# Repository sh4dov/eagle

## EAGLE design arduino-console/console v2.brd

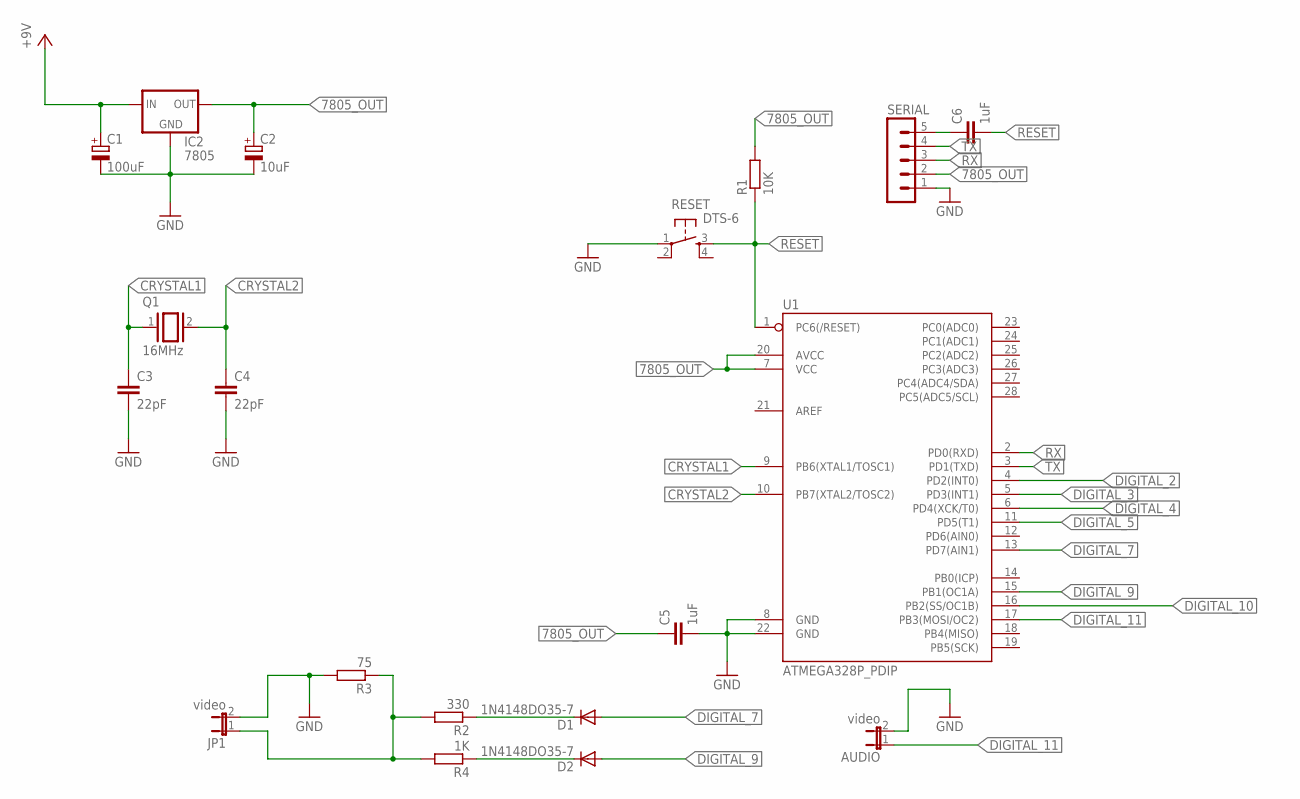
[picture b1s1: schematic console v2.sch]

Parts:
AUDIO: video; JP1
C1: 100uF; E2,5-6E
C2: 10uF; E2,5-6E
C3, C4: 22pF; C2.5-3
C5, C6: 1uF; C2.5-3
D1, D2: 1N4148DO35-7; DO35-7
IC2: 7805; 78MXXL
JP1: video; JP1
Q1: 16MHz; QS
R1: 10K; 0204/5
R2: 330; 0204/5
R3: 75; 0204/5
R4: 1K; 0204/5
RESET: DTS-6
SERIAL: MA05-1
U1: ATMEGA328P_PDIP; DIL28-3

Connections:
7805_OUT: C2.+, C5.1, IC2.OUT, R1.2, SERIAL.2, U1.7 (VCC), U1.20 (AVCC)
CRYSTAL1: C3.1, Q1.1, U1.9 (PB6(XTAL1/TOSC1))
CRYSTAL2: C4.1, Q1.2, U1.10 (PB7(XTAL2/TOSC2))
DIGITAL_2: U1.4 (PD2(INT0))
DIGITAL_3: U1.5 (PD3(INT1))
DIGITAL_4: U1.6 (PD4(XCK/T0))
DIGITAL_5: U1.11 (PD5(T1))
DIGITAL_7: D1.A, U1.13 (PD7(AIN1))
DIGITAL_9: D2.A, U1.15 (PB1(OC1A))
DIGITAL_10: U1.16 (PB2(SS/OC1B))
DIGITAL_11: AUDIO.1, U1.17 (PB3(MOSI/OC2))
GND: AUDIO.2, C1.-, C2.-, C3.2, C4.2, C5.2, IC2.GND, JP1.2, R3.2, RESET.1, SERIAL.1, U1.8 (GND), U1.22 (GND)
unnamed: D1.C, R2.1
unnamed: D2.C, R4.1
unnamed: JP1.1, R2.2, R3.1, R4.2
unnamed: C6.1, SERIAL.5
RESET: C6.2, R1.1, RESET.3, U1.1 (PC6(/RESET))
RX: SERIAL.3, U1.2 (PD0(RXD))
TX: SERIAL.4, U1.3 (PD1(TXD))
VCC: C1.+, IC2.IN

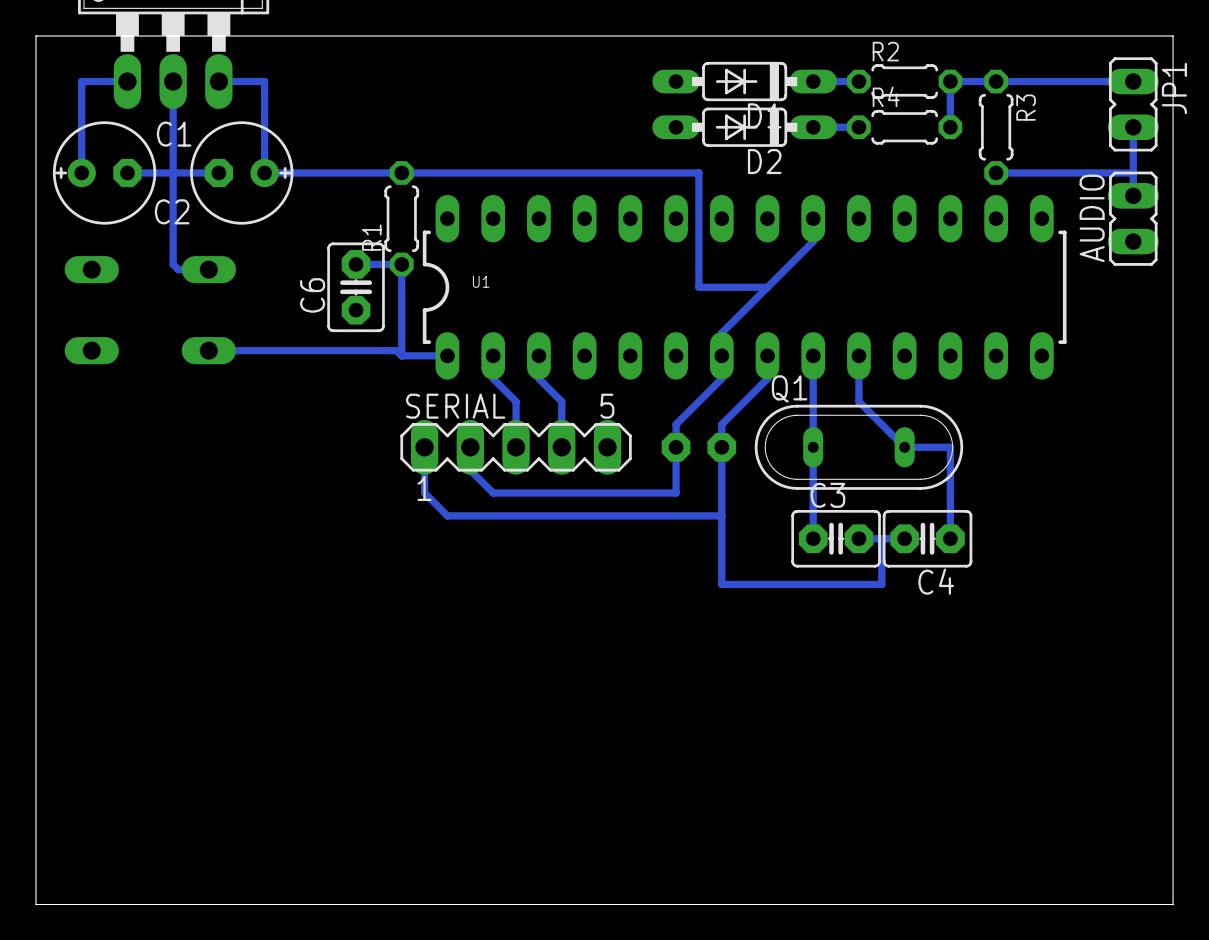
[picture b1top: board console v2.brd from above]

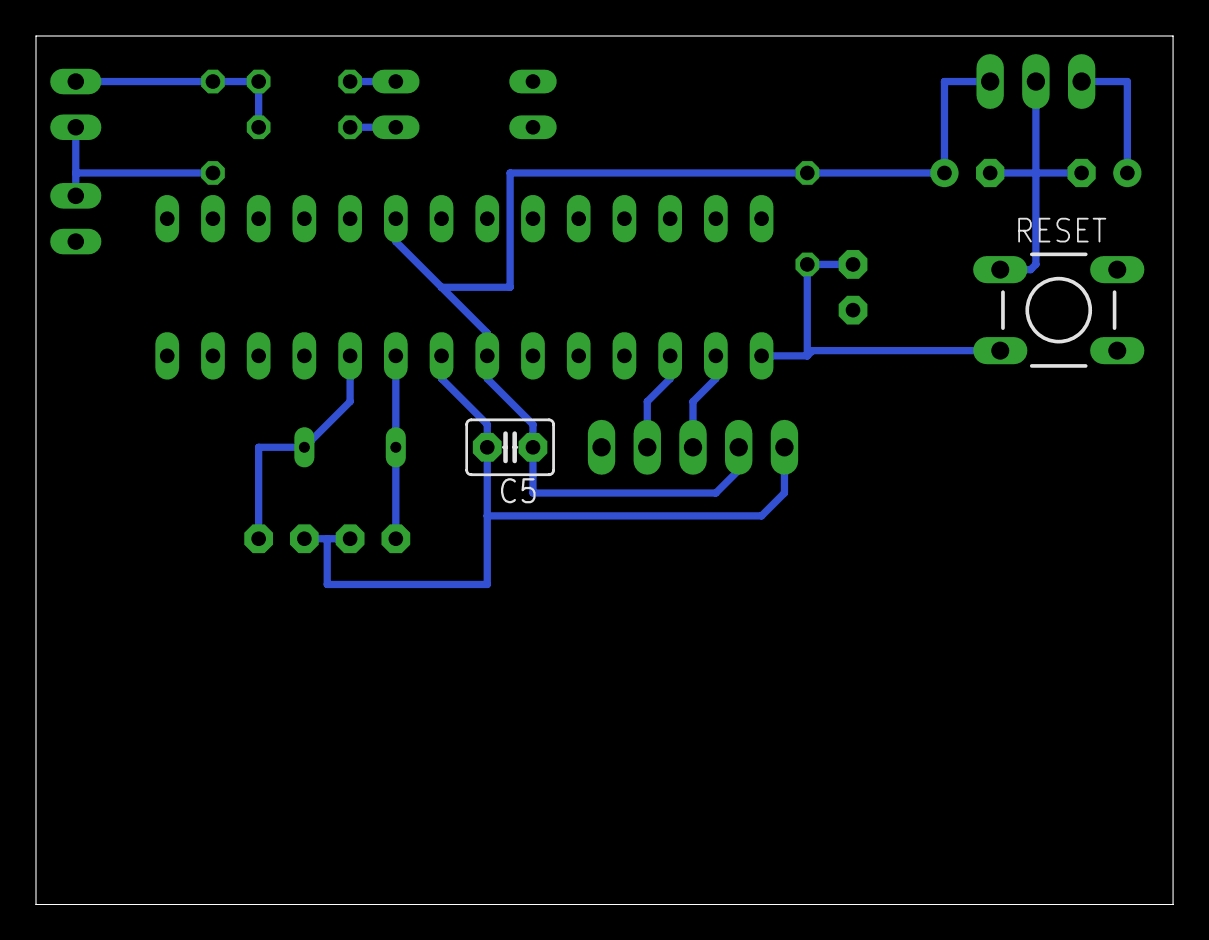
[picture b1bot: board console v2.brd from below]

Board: 2 copper layers, 63.2 x 48.2 mm, 19 parts (2 on the bottom side), 15 nets.

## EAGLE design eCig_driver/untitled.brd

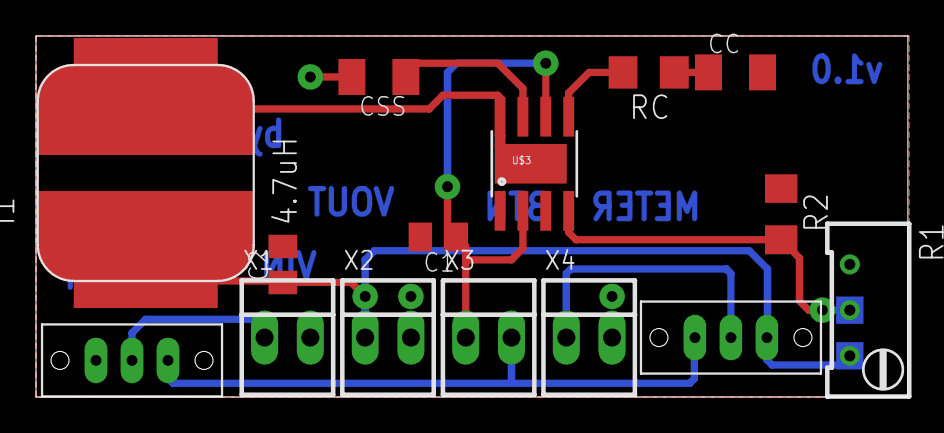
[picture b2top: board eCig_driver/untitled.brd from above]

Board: 2 copper layers, 48.4 x 20.1 mm, 15 parts (0 on the bottom side), 11 nets.

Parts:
C1: 10uF; C0805K
C2: 22uf; C0805K
CC: 1nf; C1206K
CSS: 10nf; C1206K
I1: 4.7uH; RH127
MASTER_ON: SPDT_SLIDE_SWITCH_2_PITCH
METER_SWITCH: SPDT_SLIDE_SWITCH_2_PITCH
R1: 100k; RTRIM64W
R2: 10K; R1206
RC: 22k; R1206
U$3: AOZ1051PI
X1: VIN; 22-23-2021
X2: VOUT; 22-23-2021
X3: button; 22-23-2021
X4: voltmeter; 22-23-2021

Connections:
GND: C1.2, C2.2, CC.2, CSS.2, R2.1, U$3.1, U$3.3, X1.2, X2.2, X4.2
unnamed: RC.2, U$3.5
unnamed: CC.1, RC.1
unnamed: R1.2, R2.2, U$3.4
unnamed: CSS.1, U$3.7
unnamed: METER_SWITCH.COMMON, X4.1
unnamed: I1.P$1, U$3.8, U$3.P$1, U$3.P$2
unnamed: C2.1, I1.P$2, METER_SWITCH.S1, R1.3, X2.1
unnamed: MASTER_ON.COMMON, X1.1
unnamed: MASTER_ON.S1, METER_SWITCH.S0, X3.2
VCC: C1.1, U$3.2, U$3.6, X3.1

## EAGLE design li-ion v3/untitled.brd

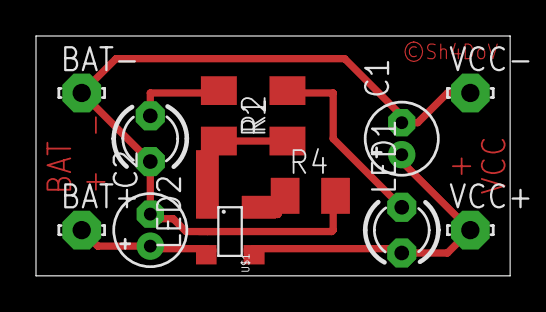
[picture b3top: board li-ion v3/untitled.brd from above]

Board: 2 copper layers, 26.3 x 13.3 mm, 12 parts (0 on the bottom side), 7 nets.

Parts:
BAT+: LSP10
BAT-: LSP10
C1, C2: 10u; E1,8-4
LED1: red; LED3MM
LED2: green; LED3MM
R1, R2: 1k; M1206
R4: 2k; M1206
U$1: mcp73831; 5PIN_SOT23
VCC+: LSP10
VCC-: LSP10

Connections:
GND: BAT-.MP, C1.-, C2.-, LED2.K, R4.2, U$1.P$2, VCC-.MP
unnamed: R4.1, U$1.P$5
unnamed: LED1.K, R1.2
unnamed: R1.1, R2.2, U$1.P$1
unnamed: LED2.A, R2.1
unnamed: BAT+.MP, C2.+, U$1.P$3
VCC: C1.+, LED1.A, U$1.P$4, VCC+.MP

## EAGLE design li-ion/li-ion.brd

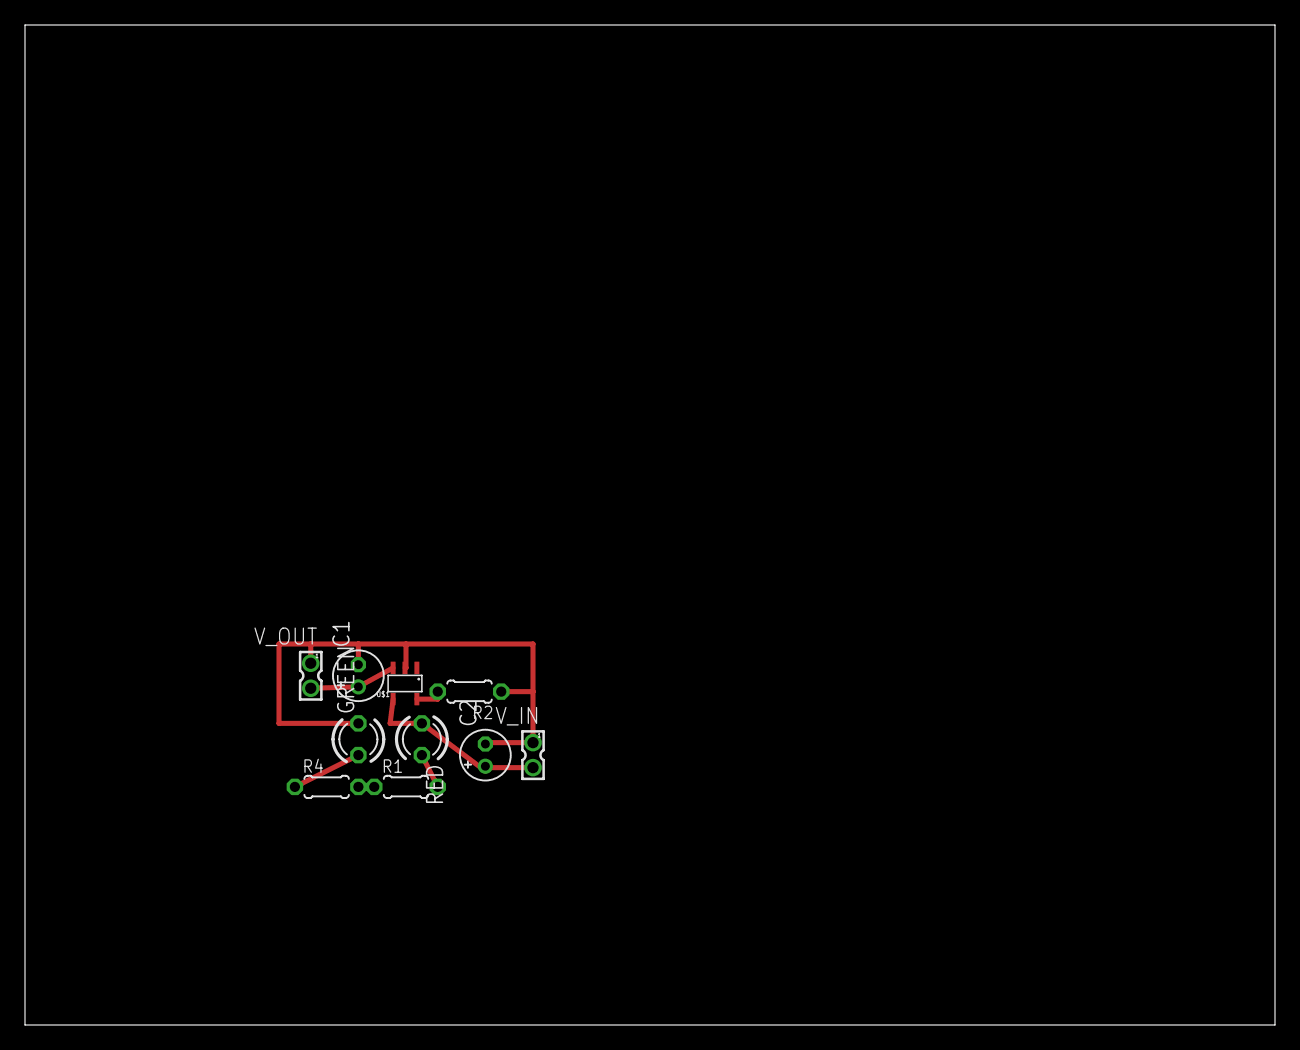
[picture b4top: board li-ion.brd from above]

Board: 2 copper layers, 100.0 x 80.0 mm, 10 parts (0 on the bottom side), 7 nets.

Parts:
C1, C2: 10u; E1,8-4
GREEN: LED3MM
R1, R4: 1k; 0204/5
R2: 2k; 0204/5
RED: LED3MM
U$1: 5PIN_SOT23
V_IN: 332-02
V_OUT: 332-02

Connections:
GND: C1.-, C2.-, GREEN.K, R2.1, U$1.P$2, V_IN.1, V_OUT.1
unnamed: C1.+, U$1.P$3, V_OUT.2
unnamed: R2.2, U$1.P$5
unnamed: R1.1, R4.2, U$1.P$1
unnamed: R1.2, RED.K
unnamed: GREEN.A, R4.1
VCC: C2.+, RED.A, U$1.P$4, V_IN.2

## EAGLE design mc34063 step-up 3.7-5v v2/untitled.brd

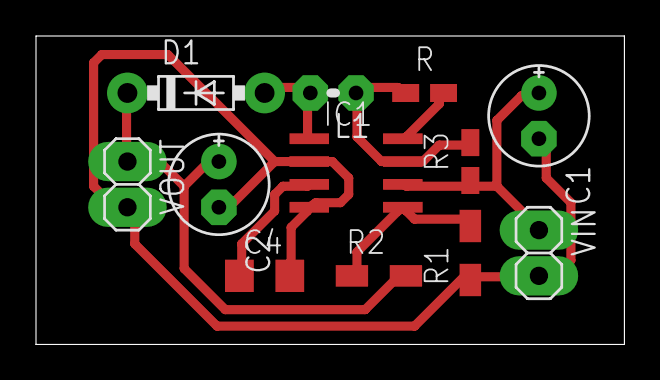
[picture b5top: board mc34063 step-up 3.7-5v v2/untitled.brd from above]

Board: 2 copper layers, 32.7 x 17.1 mm, 12 parts (0 on the bottom side), 8 nets.

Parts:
C1: 100u; E2,5-6E
C2: 330u; E2,5-6E
C4: 1500pF; C1206
D1: 1N5819-B; DO41-7.6
IC1: MC34063AD; SOIC8
L1: 170uH; 0204V
R: 180; R0805W
R1: 1k; R1206W
R2: 3k; R1206W
R3: 0; R0805W
VIN: 1X02
VOUT: 1X02

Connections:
GND: C1.-, C2.-, C4.2, IC1.2, IC1.4, R1.1, VIN.2, VOUT.2
unnamed: D1.A, IC1.1, L1.2
unnamed: C2.+, D1.C, R2.2, VOUT.1
unnamed: C4.1, IC1.3
unnamed: IC1.5, R1.2, R2.1
unnamed: IC1.7, L1.1, R.1, R3.2
unnamed: IC1.8, R.2
VCC: C1.+, IC1.6, R3.1, VIN.1

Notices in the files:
li-ion v3/untitled.brd:
©Sh4DoV
parts and their libraries:
SparkFun-DigitalIC: Licensing: Creative Commons ShareAlike 4.0 International - https://creativecommons.org/licenses/by-sa/4.0
